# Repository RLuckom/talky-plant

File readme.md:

## Talky-plant: a sensor connector for esp-8266 NodeMCU v3

Board files for my ongoing project to create internet-connected sensors. For
the ESP8266 code, see [extra sensory](https://github.com/RLuckom/extra-sensory)

This is a kicad project containing a board layout for a daughterboard to connect 
the NodeMCU v3 board to a DHT11 temperature / humidity sensor, a YL-69 soil 
moisture sensor, and a photoresistor to measure sunlight levels.

TODO:

1. The resistor values listed in the schematic don't take into account either
   the voltage drop across the diodes or the values resistors actually come in.
   The resolution is way below what should be possible and I don't see the full
   range of adc values from either photoresistor or YL-69.

2. Everything I've read suggests that soil moisture sensors are extremely
   short-lived devices. I have to characterize them better, and in the hardware
   design I should plan for having to switch out the fork part that goes in the
   soil.

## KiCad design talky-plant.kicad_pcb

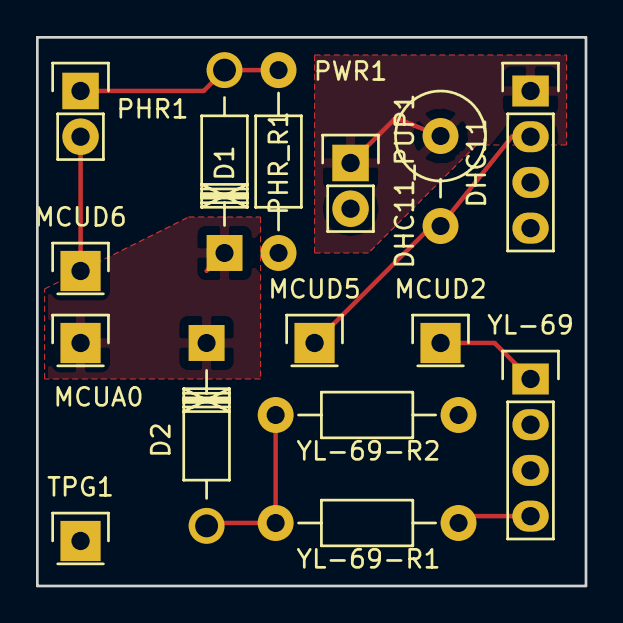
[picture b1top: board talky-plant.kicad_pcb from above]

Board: 2 copper layers, 30.5 x 30.5 mm, 15 parts (0 on the bottom side), 9 nets.

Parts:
D1, D2: IN5817; Diode_DO-41_SOD81_Horizontal_RM10
DHC11: CONN_01X04; Pin_Header_Straight_1x04
DHC11_PUP1: 10K; Resistor_Vertical_RM5mm
MCUA0: CONN_01X01; Pin_Header_Straight_1x01
MCUD2, MCUD5, MCUD6: CONN_01X01; Pin_Header_Straight_1x01
PHR1: CONN_01X02; Pin_Header_Straight_1x02
PHR_R1: 200R; Resistor_Horizontal_RM10mm
PWR1: CONN_01X02; Pin_Header_Straight_1x02
TPG1: CONN_01X01; Pin_Header_Straight_1x01
YL-69: CONN_01X04; Pin_Header_Straight_1x04
YL-69-R1: 10K; Resistor_Horizontal_RM10mm
YL-69-R2: 5K; Resistor_Horizontal_RM10mm

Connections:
+3V3: DHC11.1, DHC11_PUP1.1, PWR1.1
GND: DHC11.4, PHR_R1.1, PWR1.2, TPG1.1, YL-69.2, YL-69-R2.1
unnamed: D1.1, D2.1, MCUA0.1
unnamed: D1.2, PHR1.1, PHR_R1.2
unnamed: D2.2, YL-69-R1.2, YL-69-R2.2
unnamed: DHC11.2, DHC11_PUP1.2, MCUD5.1
unnamed: MCUD2.1, YL-69.1
unnamed: MCUD6.1, PHR1.2
unnamed: YL-69.4, YL-69-R1.1
